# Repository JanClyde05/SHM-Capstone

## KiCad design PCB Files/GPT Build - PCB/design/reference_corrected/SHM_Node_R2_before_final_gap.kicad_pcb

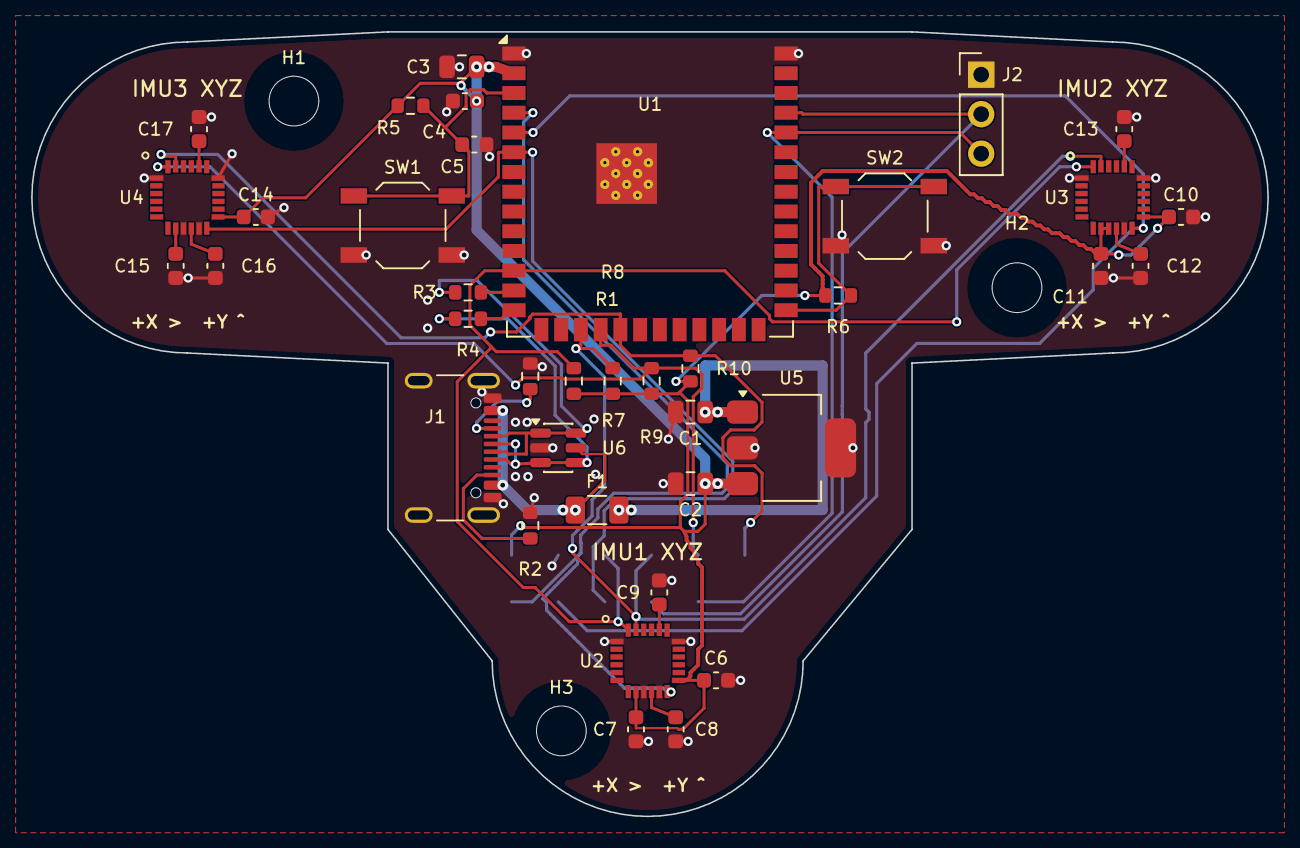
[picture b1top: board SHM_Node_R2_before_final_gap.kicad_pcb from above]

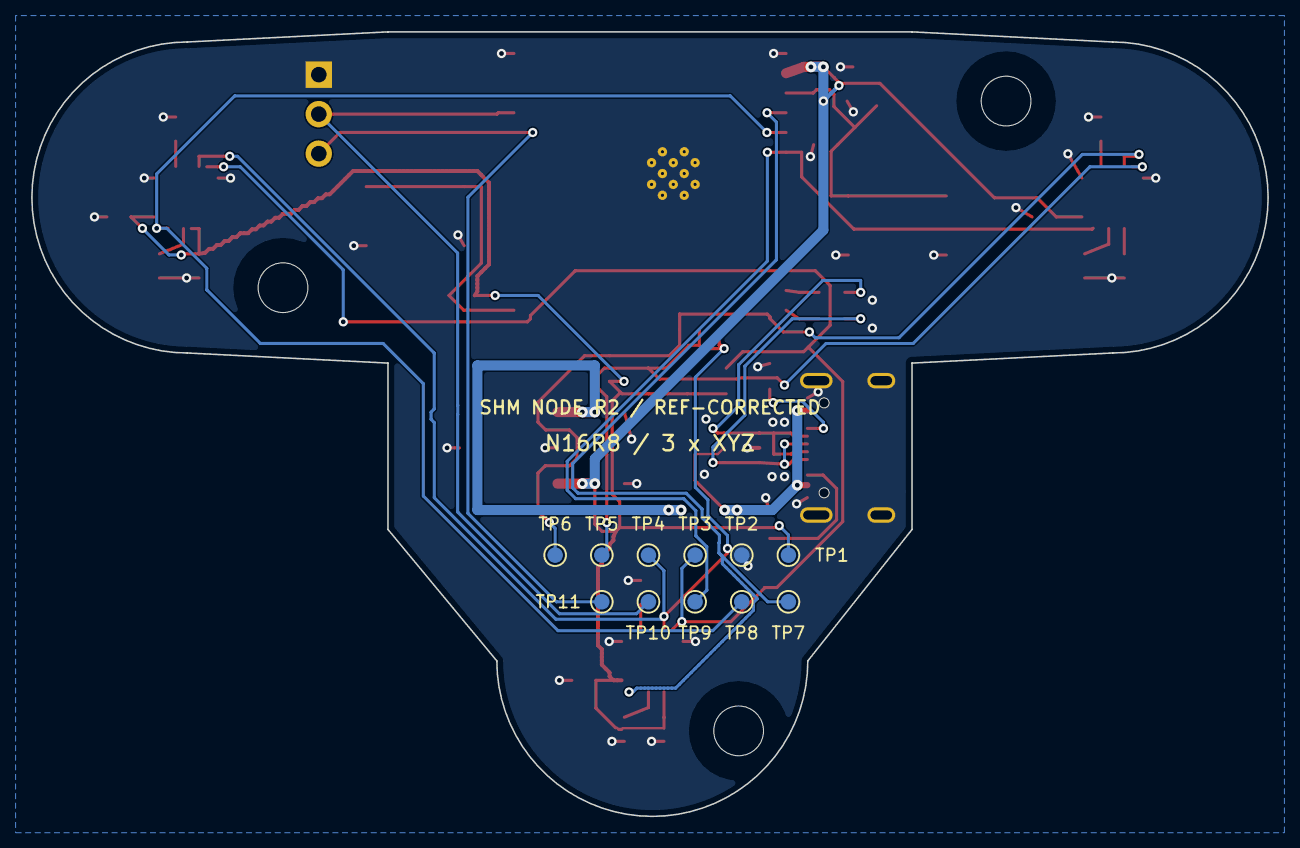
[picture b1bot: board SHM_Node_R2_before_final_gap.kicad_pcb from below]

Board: 4 copper layers, 79.5 x 50.5 mm, 52 parts (11 on the bottom side), 27 nets.

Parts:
C1: 4.7uF; C_0805_2012Metric
C2, C3: 10uF; C_0805_2012Metric
C4, C6, C8, C10, C12, C14, C16: 100nF; C_0603_1608Metric
C5: 1uF; C_0603_1608Metric
C7, C11, C15: 10nF; C_0603_1608Metric
C9, C13, C17: 2.2nF; C_0603_1608Metric
F1: 0.75A HOLD; Fuse_1206_3216Metric
H1, H2, H3: M3 NPTH; MountingHole_3.2mm_M3
J1: USB4105-GF-A; USB_C_Receptacle_GCT_USB4105-xx-A_16P_TopMnt_Horizontal
J2: UART DEBUG (3V3 LOGIC); PinHeader_1x03_P2.54mm_Vertical
R1, R2: 5.1k 1%; R_0603_1608Metric
R3, R4: 22R; R_0603_1608Metric
R5, R6: 10k; R_0603_1608Metric
R7, R8, R9, R10: 2.2k; R_0603_1608Metric
SW1: RESET; SW_SPST_TL3342
SW2: BOOT; SW_SPST_TL3342
TP1: +3V3; TestPoint_Pad_D1.0mm
TP2: GND; TestPoint_Pad_D1.0mm
TP3: I2C0_SDA; TestPoint_Pad_D1.0mm
TP4: I2C0_SCL; TestPoint_Pad_D1.0mm
TP5: I2C1_SDA; TestPoint_Pad_D1.0mm
TP6: I2C1_SCL; TestPoint_Pad_D1.0mm
TP7: IMU1_INT; TestPoint_Pad_D1.0mm
TP8: IMU2_INT; TestPoint_Pad_D1.0mm
TP9: IMU3_INT; TestPoint_Pad_D1.0mm
TP10: UART_TX; TestPoint_Pad_D1.0mm
TP11: UART_RX; TestPoint_Pad_D1.0mm
U1: ESP32-S3-WROOM-1-N16R8; ESP32-S3-WROOM-1_Overhang
U2, U3, U4: MPU-6050; MPU6050_QFN24_NoCenterPad
U5: AP7361C-33E-13; SOT-223-3_TabPin2
U6: USBLC6-2SC6; SOT-23-6

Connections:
+3V3: C2.1, C3.1, C4.1, C6.1, C7.1, C10.1, C11.1, C14.1, C15.1, R5.1, R6.1, R7.1, R8.1, R9.1, R10.1, TP1.1, U1.2, U2.8, U2.13, U3.8, U3.9, U3.13, U4.8, U4.13, U5.3
/+5V_FUSED: C1.1, F1.2, U5.1
/BOOT: R6.2, SW2.1, U1.27
/CC1: J1.A5, R1.1
/CC2: J1.B5, R2.1
/EN: C5.1, R5.2, SW1.1, U1.3
/I2C0_SCL: R8.2, TP4.1, U1.17, U2.23, U3.23
/I2C0_SDA: R7.2, TP3.1, U1.12, U2.24, U3.24
/I2C1_SCL: R10.2, TP6.1, U1.19, U4.23
/I2C1_SDA: R9.2, TP5.1, U1.18, U4.24
/IMU1_CPOUT: C9.1, U2.20
/IMU1_INT: TP7.1, U1.4, U2.12
/IMU1_REGOUT: C8.1, U2.10
/IMU2_CPOUT: C13.1, U3.20
/IMU2_INT: TP8.1, U1.5, U3.12
/IMU2_REGOUT: C12.1, U3.10
/IMU3_CPOUT: C17.1, U4.20
/IMU3_INT: TP9.1, U1.6, U4.12
/IMU3_REGOUT: C16.1, U4.10
/UART_RX: J2.3, TP11.1, U1.36
/UART_TX: J2.2, TP10.1, U1.37
/USB_DM: J1.A7, J1.B7, R3.1, U6.1, U6.6
/USB_DM_MCU: R3.2, U1.13
/USB_DP: J1.A6, J1.B6, R4.1, U6.3, U6.4
/USB_DP_MCU: R4.2, U1.14
/VBUS_USB: F1.1, J1.A4, J1.A9, J1.B4, J1.B9, U6.5
GND: C1.2, C2.2, C3.2, C4.2, C5.2, C6.2, C7.2, C8.2, C9.2, C10.2, C11.2, C12.2, C13.2, C14.2, C15.2, C16.2, C17.2, J1.A1, J1.A12, J1.B1, J1.B12, J1.SH, J2.1, R1.2, R2.2, SW1.2, SW2.2, TP2.1, U1.1, U1.40, U1.41, U2.1, U2.9, U2.11, U2.18, U3.1, U3.11, U3.18, U4.1, U4.9, U4.11, U4.18, U5.2, U6.2
